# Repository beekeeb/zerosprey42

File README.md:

# Zerosprey42 Keyboard

Zerosprey42 Keyboard is a 42-key, wired, beginner friendly, choc v1 hotswap, MonoBlockSplit (Unibody), column-staggered, DIY low-profile mechanical keyboard. It balances between portability and ergonomics with a sleek travel case. This is a remix of ebastler‘s [osprey](https://github.com/ebastler/osprey) with a low cost RP2040-Zero. 

The development of this project is sponsored by [PCBWay](https://pcbway.com/g/beekeeb) (affiliate link).

## Quick Links

* [Build guide](https://docs.beekeeb.com/zerosprey42-keyboard#build-guide)
* [Precompiled firmware](https://docs.beekeeb.com/zerosprey42-keyboard#precompiled-firmware)
* [beekeeb showcase](https://showcase.beekeeb.com/zerosprey42-keyboard/)

## Features

* MCU Board - WaveShare RP2040-Zero
	* It includes a powerful RP2040 MCU with a lot of flash memory (2MB), so you can enable many QMK features and layers without worrying about the firmware size.
* Easier to solder (for the DIY soldering option)
	* There are very few components/pins to solder for the basic version. You will need to solder diodes, hot swap sockets, and the castellated holes for the RP2040-Zero.
* Choc spacing
	* Key switches are arranged tighter than the standard spacing.
* Ergonomics
	* Slightly angled sides, with a bigger thumb key.
* Monoblock Enclosure for Portability
	* There is an elegant case modified from the original osprey keyboard. It includes a top case, switch plate and a bottom case.
* Firmware
	* QMK and Vial are supported. For advanced users, you should be able to use other firmwares including ZMK, KMK (Python-based), PRK (Ruby-based) and keyberon (Rust-based)

## Bill of Materials (BOM)

Quantity | Item | Notes
--- | --- | ---
1 | Zerosprey42 PCB
1 | WaveShare RP2040-Zero
42 | 1N4148 SOD123 diodes
42 | CPG135001S30 hotswap sockets for choc v1 PG1350
42 | choc v1 key switches
42 | choc v1 keycaps | "choc spacing" required

## Ordering Parts

[DIY kits](https://shop.beekeeb.com/product/zerosprey42-monoblock-rp2040-keyboard/) and [prebuilt keyboards](https://shop.beekeeb.com/product/zerosprey42-monoblock-rp2040-keyboard/) are available at https://beekeeb.shop

If you prefer getting the parts by yourself, you can order the PCB from [PCBWay](https://www.pcbway.com/project/shareproject/Zerosprey42_Keyboard_23ae2219.html) or other PCB manufacturers. 

## Firmware

* [QMK](https://github.com/qmk/qmk_firmware)
* [Vial](https://github.com/beekeeb/vial-qmk-zerosprey42) (based on QMK)
* [ZMK](https://github.com/tubbytwins/zmk-config-zerosprey42) by [tubbytwins](https://github.com/tubbytwins)

For advanced users, other firmwares including KMK (Python/CircuitPython), PRK (Ruby), keyberon (Rust) should be possible.

Precompiled firmware can be found at https://docs.beekeeb.com/zerosprey42-keyboard.

## Boards Preview

## License

Logos, external symbols and footprints are not covered by the LICENSE in this repo.

## Sponsors

This open source hardware project is sponsored by

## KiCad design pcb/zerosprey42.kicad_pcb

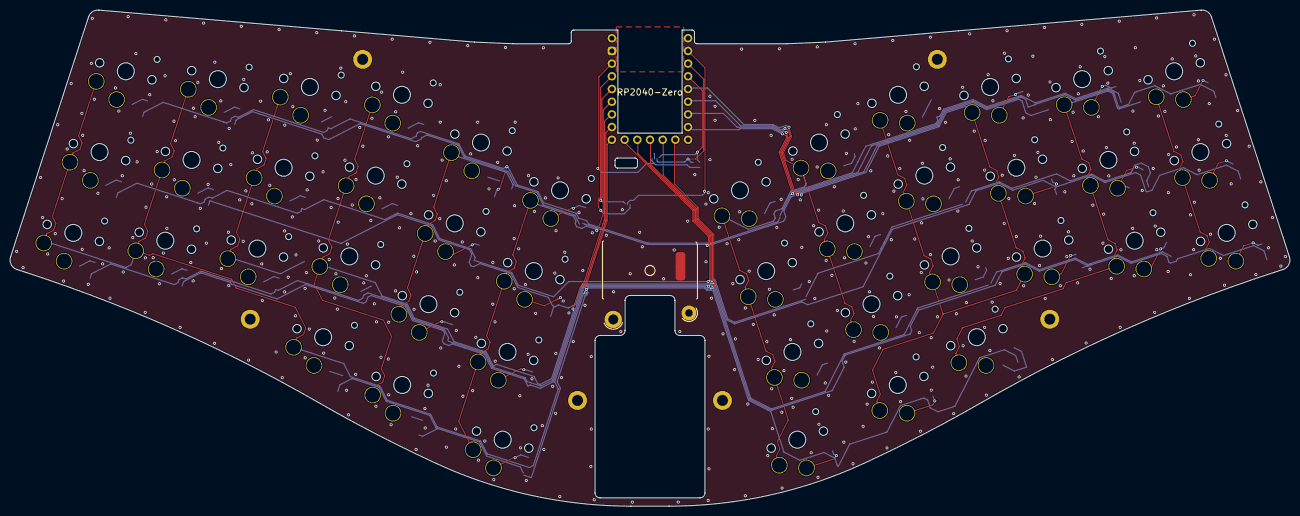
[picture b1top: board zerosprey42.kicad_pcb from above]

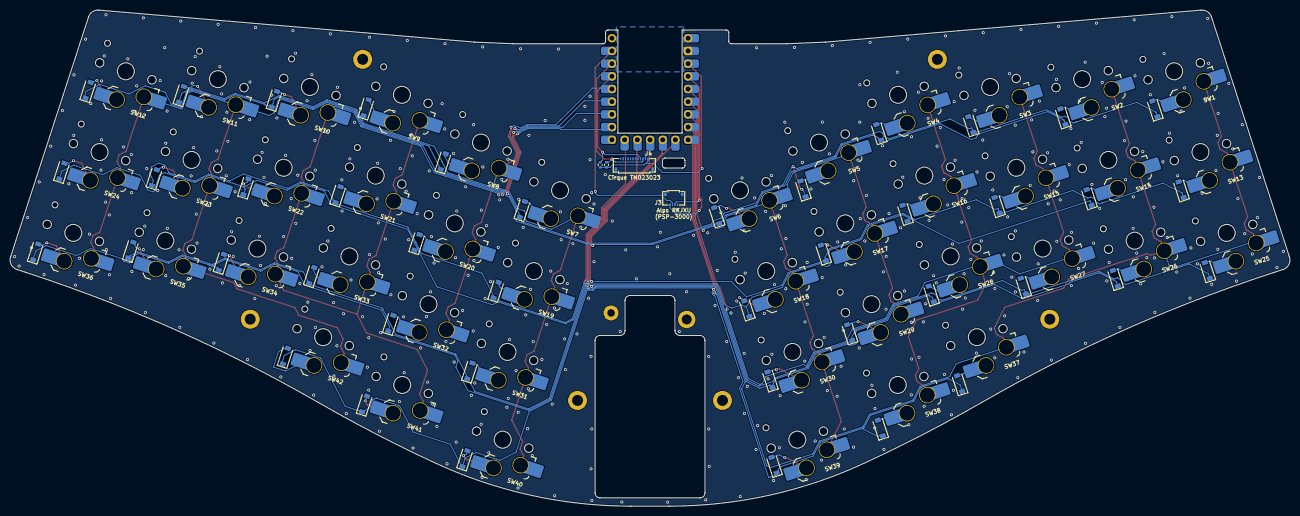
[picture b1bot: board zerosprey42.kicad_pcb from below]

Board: 2 copper layers, 256.0 x 99.2 mm, 96 parts (92 on the bottom side), 62 nets.

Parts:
D1, D2, D3, D4, D5, D6, D7, D8, D9, D10, D11, D12, D13, D14, D15, D16, D17, D18, D19, D20, D21, D22, D23, D24, D25, D26, D27, D28, D29, D30, D31, D32, D33, D34, D35, D36, D37, D38, D39, D40, D41, D42: 1N4148WT; D_SOD-123
H1, H2, H3, H4, H5, H6: M2; MountingHole_2.2mm_M2_DIN965_Pad
J3: FH33J-4S-0.5SH; CON_FH33J-4S-0.5SH
J4: FH33J-12S-0.5SH; CON_FH33J-12S-0.5SH
PNT1: MountingHole_Pad; PNT_RKJXU1210006
R1, R2: 10 kOhm; R_0402_1005Metric
SW1, SW2, SW3, SW4, SW5, SW6, SW7, SW8, SW9, SW10, SW11, SW12, SW13, SW14, SW15, SW16, SW17, SW18, SW19, SW20, SW21, SW22, SW23, SW24, SW25, SW26, SW27, SW28, SW29, SW30, SW31, SW32, SW33, SW34, SW35, SW36, SW37, SW38, SW41, SW42: CPG135001S30; SW_choc_HS_1u
SW39, SW40: CPG135001S30; SW_choc_HS_1.5u
U2: RP2040-Zero; rp2040-zero-back

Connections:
GND: H1.1, H2.1, H3.1, H4.1, H5.1, H6.1, J3.1, J3.MP (MountPin), J4.11, J4.MP (MountPin), PNT1.MP, U2.2 (GND)
unnamed: D1.2 (A), SW1.2
unnamed: D2.2 (A), SW2.2
unnamed: D3.2 (A), SW3.2
unnamed: D4.2 (A), SW4.2
unnamed: D5.2 (A), SW5.2
unnamed: D6.2 (A), SW6.2
unnamed: D7.2 (A), SW7.2
unnamed: D8.2 (A), SW8.2
unnamed: D9.2 (A), SW9.2
unnamed: D10.2 (A), SW10.2
unnamed: D11.2 (A), SW11.2
unnamed: D12.2 (A), SW12.2
unnamed: D13.2 (A), SW13.2
unnamed: D14.2 (A), SW14.2
unnamed: D15.2 (A), SW15.2
unnamed: D16.2 (A), SW16.2
unnamed: D17.2 (A), SW17.2
unnamed: D18.2 (A), SW18.2
unnamed: D19.2 (A), SW19.2
unnamed: D20.2 (A), SW20.2
unnamed: D21.2 (A), SW21.2
unnamed: D22.2 (A), SW22.2
unnamed: D23.2 (A), SW23.2
unnamed: D24.2 (A), SW24.2
unnamed: D25.2 (A), SW25.2
unnamed: D26.2 (A), SW26.2
unnamed: D27.2 (A), SW27.2
unnamed: D28.2 (A), SW28.2
unnamed: D29.2 (A), SW29.2
unnamed: D30.2 (A), SW30.2
unnamed: D31.2 (A), SW31.2
unnamed: D32.2 (A), SW32.2
unnamed: D33.2 (A), SW33.2
unnamed: D34.2 (A), SW34.2
unnamed: D35.2 (A), SW35.2
unnamed: D36.2 (A), SW36.2
unnamed: D37.2 (A), SW37.2
unnamed: D38.2 (A), SW38.2
unnamed: D39.2 (A), SW39.2
unnamed: D40.2 (A), SW40.2
unnamed: D41.2 (A), SW41.2
unnamed: D42.2 (A), SW42.2
PNTEN: J3.3, U2.22 (GP1)
PNTX: J3.2, U2.5 (GP28)
PNTY: J3.4, U2.4 (GP29)
SCL: J4.9, R1.2, U2.20 (GP3)
SDA: J4.10, R2.2, U2.21 (GP2)
VDD: J4.12, R1.1, R2.1, U2.3 (3V3)
c0: SW1.1, SW2.1, SW13.1, SW14.1, SW25.1, SW26.1, SW37.1, U2.8 (GP15)
c1: SW3.1, SW4.1, SW15.1, SW16.1, SW27.1, SW28.1, SW38.1, U2.7 (GP26)
c2: SW5.1, SW6.1, SW17.1, SW18.1, SW29.1, SW30.1, SW39.1, U2.6 (GP27)
c3: SW7.1, SW8.1, SW19.1, SW20.1, SW31.1, SW32.1, SW40.1, U2.19 (GP4)
c4: SW9.1, SW10.1, SW21.1, SW22.1, SW33.1, SW34.1, SW41.1, U2.18 (GP5)
c5: SW11.1, SW12.1, SW23.1, SW24.1, SW35.1, SW36.1, SW42.1, U2.17 (GP6)
r0: D1.1 (K), D3.1 (K), D5.1 (K), D7.1 (K), D9.1 (K), D11.1 (K), U2.16 (GP7)
r1: D2.1 (K), D4.1 (K), D6.1 (K), D8.1 (K), D10.1 (K), D12.1 (K), U2.10 (GP13)
r2: D13.1 (K), D15.1 (K), D17.1 (K), D19.1 (K), D21.1 (K), D23.1 (K), U2.11 (GP12)
r3: D14.1 (K), D16.1 (K), D18.1 (K), D20.1 (K), D22.1 (K), D24.1 (K), U2.12 (GP11)
r4: D25.1 (K), D27.1 (K), D29.1 (K), D31.1 (K), D33.1 (K), D35.1 (K), U2.13 (GP10)
r5: D26.1 (K), D28.1 (K), D30.1 (K), D32.1 (K), D34.1 (K), D36.1 (K), U2.14 (GP9)
r6: D37.1 (K), D38.1 (K), D39.1 (K), D40.1 (K), D41.1 (K), D42.1 (K), U2.9 (GP14)

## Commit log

2022-11-21 Add ZMK config by tubbytwins
